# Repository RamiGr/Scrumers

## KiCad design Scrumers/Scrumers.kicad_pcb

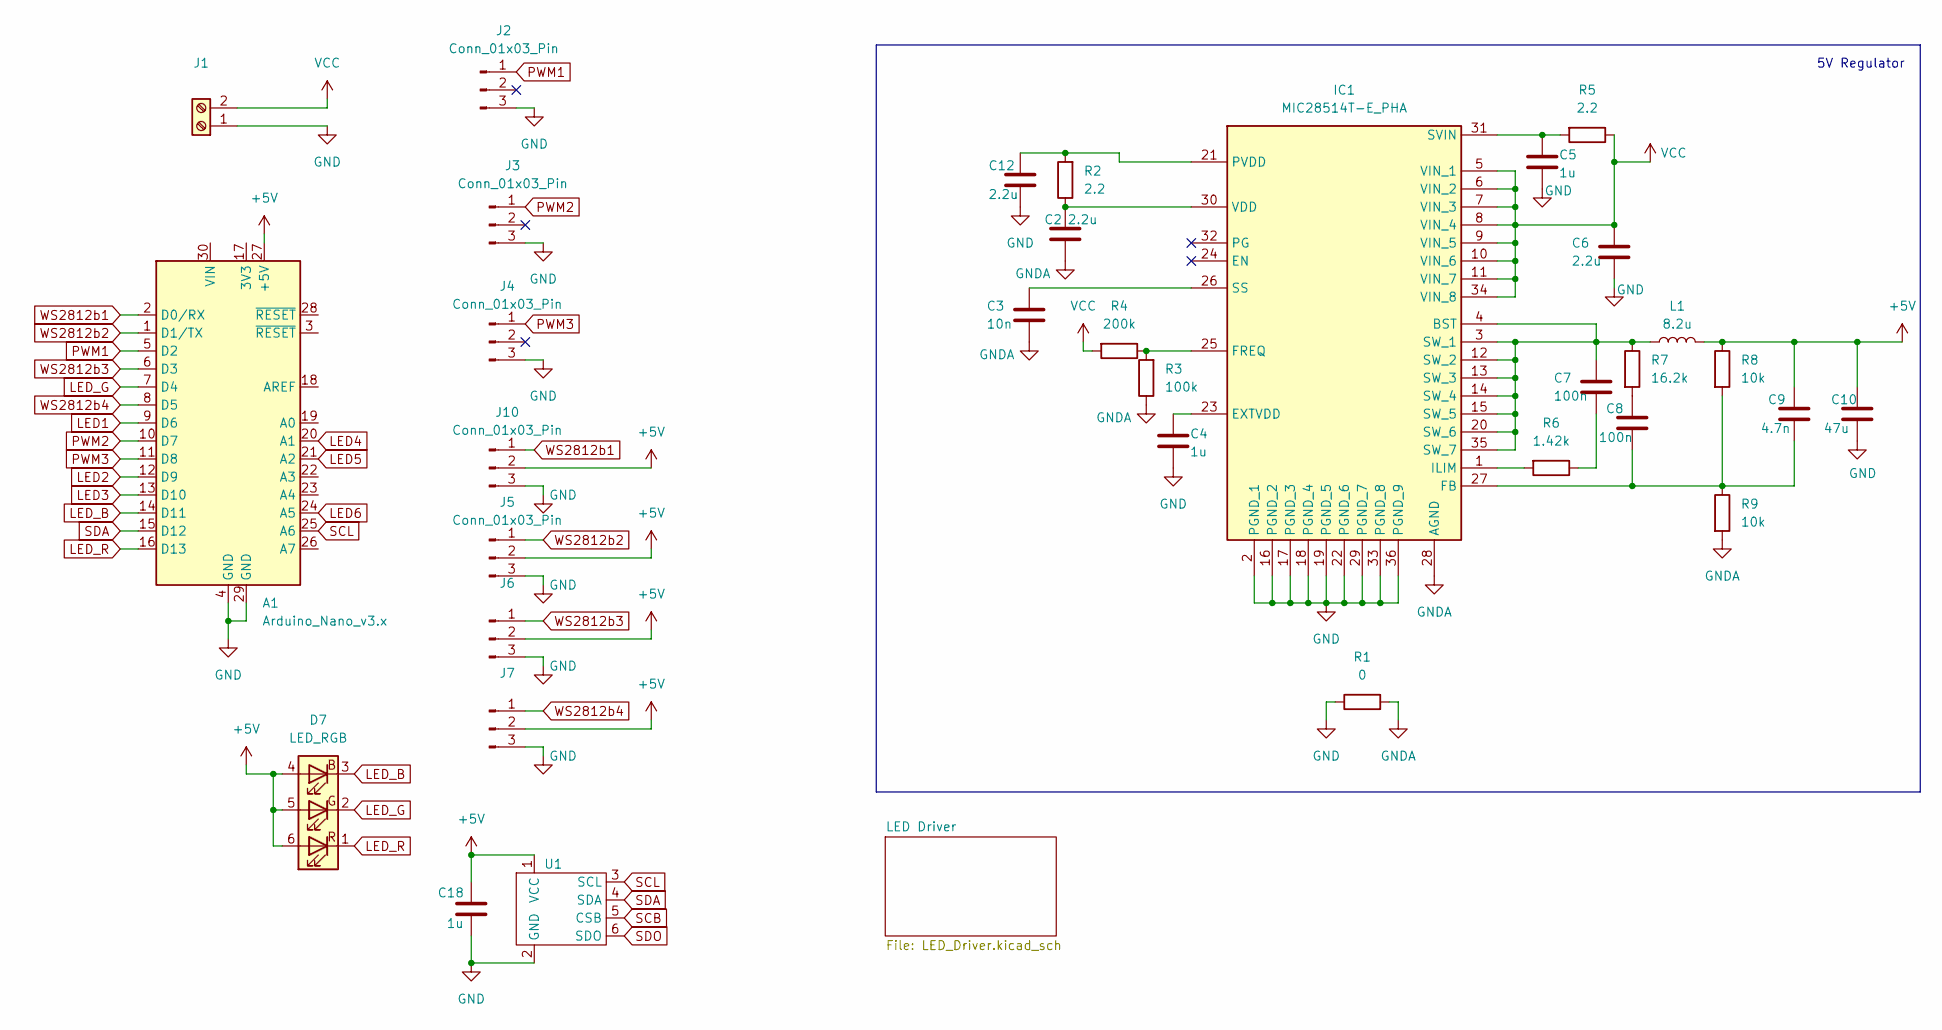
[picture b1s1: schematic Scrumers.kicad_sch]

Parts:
A1: Arduino_Nano_v3.x; Arduino_Nano
C2, C12: 2.2u; C_0805_2012Metric; Mouser No. 810-C2012X7R2225K125
C3: 10n; C_0805_2012Metric
C4, C5, C18: 1u; C_0805_2012Metric
C6: 2.2u; C_0805_2012Metric
C7, C8: 100n; C_0805_2012Metric
C9: 4.7n; C_0805_2012Metric
C10: 47u; C_0805_2012Metric
D7: LED_RGB; LED_RGB_5050-6
IC1: MIC28514T-E_PHA; MIC28514TEPHA; Mouser Part Number 579-MIC28514T-E/PHA
J1: Screw_Terminal_01x02; AMASS_XT60PW-M_1x02_P7.20mm_Horizontal
J2, J3, J4, J5, J6, J7, J10: Conn_01x03_Pin; PinHeader_1x03_P2.54mm_Horizontal
L1: 8.2u; INDPM8884X400N; Mouser No. 652-SRP8540A-8R2M
R1: 0; R_0805_2012Metric
R2, R5: 2.2; R_0805_2012Metric
R3: 100k; R_0805_2012Metric
R4: 200k; R_0805_2012Metric
R6: 1.42k; R_0805_2012Metric
R7: 16.2k; R_0805_2012Metric
R8, R9: 10k; R_0805_2012Metric
U1: Luftdruck_6

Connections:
+5V: A1.27 (+5V), C9.1, C10.1, C18.1, D7.4 (BA), D7.5 (GA), D7.6 (RA), J5.2, J6.2, J7.2, J10.2, L1.2, R8.1, U1.1 (VCC)
GND: A1.4 (GND), A1.29 (GND), C4.2, C5.2, C6.2, C10.2, C12.2, C18.2, IC1.2 (PGND_1), IC1.16 (PGND_2), IC1.17 (PGND_3), IC1.18 (PGND_4), IC1.19 (PGND_5), IC1.22 (PGND_6), IC1.29 (PGND_7), IC1.33 (PGND_8), IC1.36 (PGND_9), J1.1, J2.3, J3.3, J4.3, J5.3, J6.3, J7.3, J10.3, R1.1, U1.2 (GND); also elsewhere on the board
GNDA: C2.2, C3.2, IC1.28 (AGND), R1.2, R3.1, R9.2
LED1: A1.9 (D6); also elsewhere on the board
LED2: A1.12 (D9); also elsewhere on the board
LED3: A1.13 (D10); also elsewhere on the board
LED4: A1.20 (A1); also elsewhere on the board
LED5: A1.21 (A2); also elsewhere on the board
LED6: A1.24 (A5); also elsewhere on the board
LED_B: A1.14 (D11), D7.3 (BK)
LED_G: A1.7 (D4), D7.2 (GK)
LED_R: A1.16 (D13), D7.1 (RK)
unnamed: C7.2, R6.1
unnamed: C8.1, R7.2
unnamed: C7.1, IC1.3 (SW_1), IC1.4 (BST), IC1.12 (SW_2), IC1.13 (SW_3), IC1.14 (SW_4), IC1.15 (SW_5), IC1.20 (SW_6), IC1.35 (SW_7), L1.1, R7.1
unnamed: C4.1, IC1.23 (EXTVDD)
unnamed: C8.2, C9.2, IC1.27 (FB), R8.2, R9.1
unnamed: IC1.25 (FREQ), R3.2, R4.1
unnamed: IC1.1 (ILIM), R6.2
unnamed: C12.1, IC1.21 (PVDD), R2.2
unnamed: C3.1, IC1.26 (SS)
unnamed: C5.1, IC1.31 (SVIN), R5.2
unnamed: C2.1, IC1.30 (VDD), R2.1
PWM1: A1.5 (D2), J2.1
PWM2: A1.10 (D7), J3.1
PWM3: A1.11 (D8), J4.1
SCB: U1.5 (CSB)
SCL: A1.25 (A6), U1.3 (SCL)
SDA: A1.15 (D12), U1.4 (SDA)
SDO: U1.6 (SDO)
VCC: C6.1, IC1.5 (VIN_1), IC1.6 (VIN_2), IC1.7 (VIN_3), IC1.8 (VIN_4), IC1.9 (VIN_5), IC1.10 (VIN_6), IC1.11 (VIN_7), IC1.34 (VIN_8), J1.2, R4.2, R5.1; also elsewhere on the board
WS2812b1: A1.2 (D0/RX), J10.1
WS2812b2: A1.1 (D1/TX), J5.1
WS2812b3: A1.6 (D3), J6.1
WS2812b4: A1.8 (D5), J7.1

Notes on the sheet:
5V Regulator

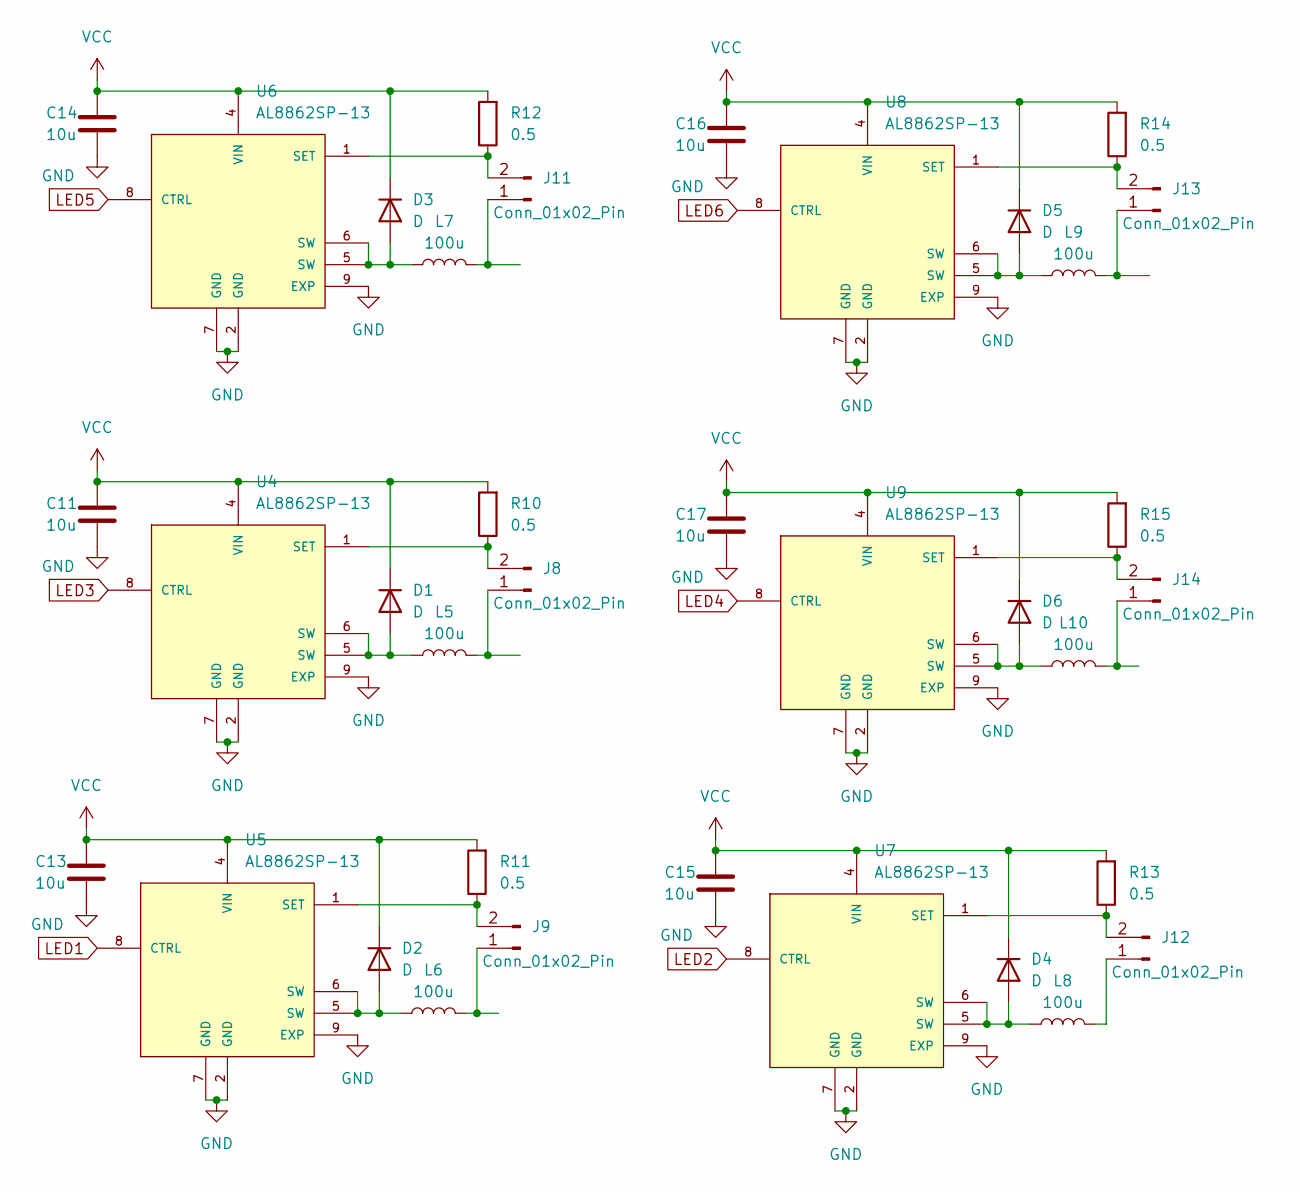
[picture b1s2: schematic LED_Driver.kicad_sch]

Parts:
C11, C13, C14, C15, C16, C17: 10u; C_1210_3225Metric; Mouser No. 810-C3225X7R2A106K25
D1, D2, D3, D4, D5, D6: D; D_SMA
J8, J9, J11, J12, J13, J14: Conn_01x02_Pin; 1851902; Mouser No. 651-1851902
L5, L6, L7, L8, L9, L10: 100u; VLS6045; Mouser No. 652-SRR1280-101M
R10, R11, R12, R13, R14, R15: 0.5; R_0805_2012Metric
U4, U5, U6, U7, U8, U9: AL8862SP-13; SOIC127P600X170-9N; Mouser No. 621-AL8862SP-13

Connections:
GND: C11.2, C13.2, C14.2, C15.2, C16.2, C17.2, U4.2 (GND), U4.7 (GND), U4.9 (EXP), U5.2 (GND), U5.7 (GND), U5.9 (EXP), U6.2 (GND), U6.7 (GND), U6.9 (EXP), U7.2 (GND), U7.7 (GND), U7.9 (EXP), U8.2 (GND), U8.7 (GND), U8.9 (EXP), U9.2 (GND), U9.7 (GND), U9.9 (EXP); also elsewhere on the board
LED1: U5.8 (CTRL); also elsewhere on the board
LED2: U7.8 (CTRL); also elsewhere on the board
LED3: U4.8 (CTRL); also elsewhere on the board
LED4: U9.8 (CTRL); also elsewhere on the board
LED5: U6.8 (CTRL); also elsewhere on the board
LED6: U8.8 (CTRL); also elsewhere on the board
unnamed: D1.2 (A), L5.1, U4.5 (SW), U4.6 (SW)
unnamed: D2.2 (A), L6.1, U5.5 (SW), U5.6 (SW)
unnamed: D3.2 (A), L7.1, U6.5 (SW), U6.6 (SW)
unnamed: D4.2 (A), L8.1, U7.5 (SW), U7.6 (SW)
unnamed: D5.2 (A), L9.1, U8.5 (SW), U8.6 (SW)
unnamed: D6.2 (A), L10.1, U9.5 (SW), U9.6 (SW)
unnamed: J8.1, L5.2
unnamed: J8.2, R10.1, U4.1 (SET)
unnamed: J9.1, L6.2
unnamed: J9.2, R11.1, U5.1 (SET)
unnamed: J11.1, L7.2
unnamed: J11.2, R12.1, U6.1 (SET)
unnamed: J12.1, L8.2
unnamed: J12.2, R13.1, U7.1 (SET)
unnamed: J13.1, L9.2
unnamed: J13.2, R14.1, U8.1 (SET)
unnamed: J14.1, L10.2
unnamed: J14.2, R15.1, U9.1 (SET)
VCC: C11.1, C13.1, C14.1, C15.1, C16.1, C17.1, D1.1 (K), D2.1 (K), D3.1 (K), D4.1 (K), D5.1 (K), D6.1 (K), R10.2, R11.2, R12.2, R13.2, R14.2, R15.2, U4.4 (VIN), U5.4 (VIN), U6.4 (VIN), U7.4 (VIN), U8.4 (VIN), U9.4 (VIN); also elsewhere on the board

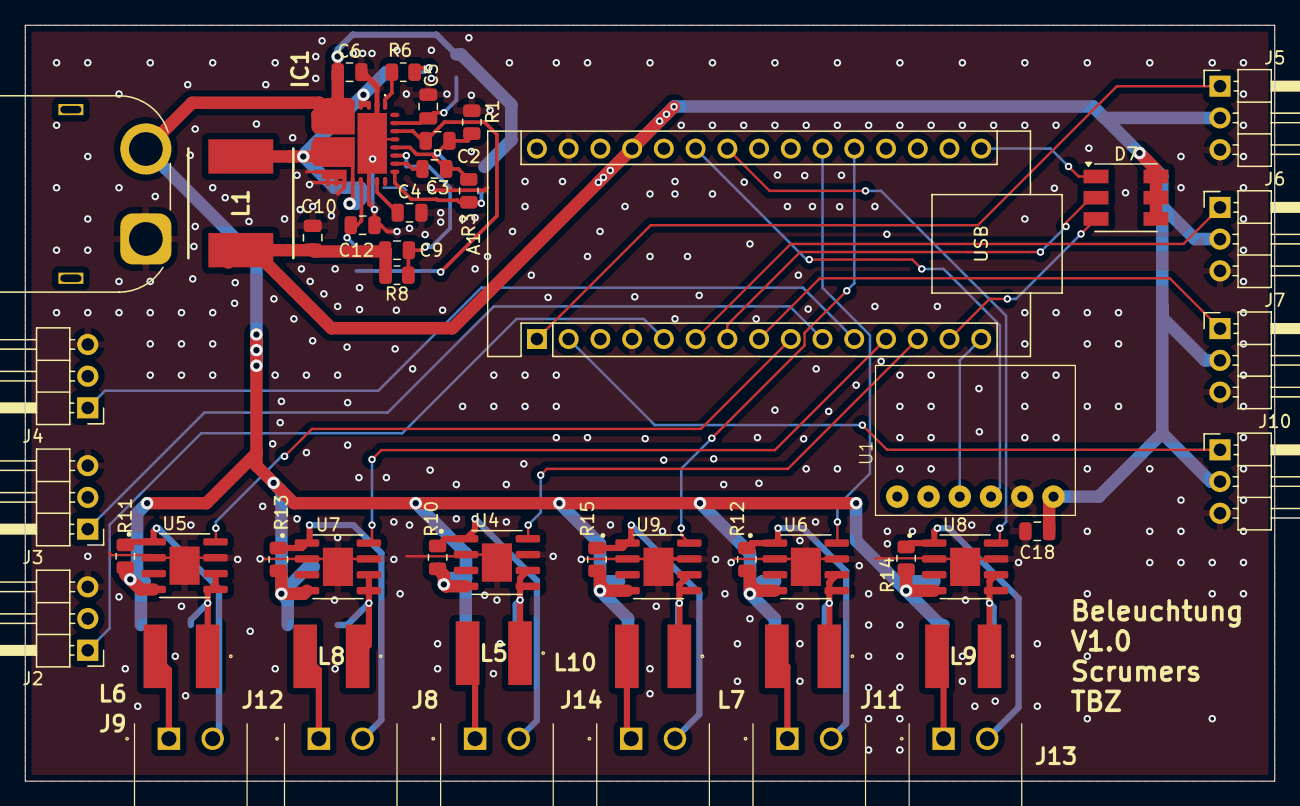
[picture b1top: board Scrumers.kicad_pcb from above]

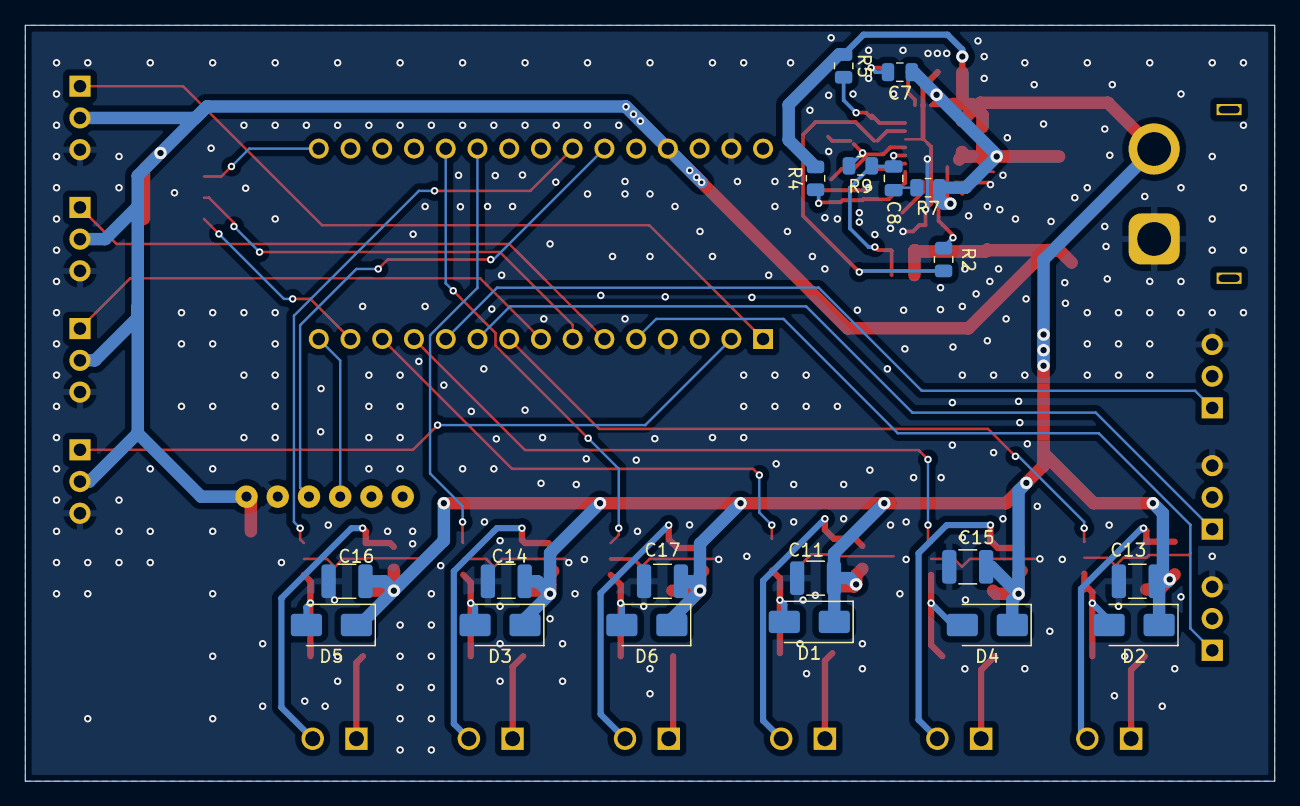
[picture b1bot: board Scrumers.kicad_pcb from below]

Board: 2 copper layers, 100.0 x 60.5 mm, 69 parts (19 on the bottom side), 51 nets.

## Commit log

2025-03-13 added kicad
2025-03-16 some changes
2025-03-20 test
2025-03-20 added voltage regulator
2025-03-26 some changes on DC DC
2025-03-26 Spannungsregler und LED Driver hinzugefügt
2025-04-03 Finish scematic
2025-04-15 layout v1 finished
